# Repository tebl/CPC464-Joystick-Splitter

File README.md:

# CPC 464 Joystick splitter

Simple passive device that breaks out the joystick port on the Amstrad CPC 464 computer so that two Atari-style joysticks can be used, it is based on an article in the magazine Amstrad Action (scans available on [CPCWiki](https://www.cpcwiki.eu/index.php/Joystick_Splitter)). Note that because there are no active components, this will not work with joysticks that have any active electronics (commonly used by autofire circuits). A second fire button has also been added, this matches the pinout usually associated with Sega Master System gamepads (will not work with the controllers for Sega Genesis or Mega Drive).

There is an additional faceplate available for this project, this is mainly there to add the appearance of putting it all in a box without breaking out a hacksaw. This is completely optional and don't serve any purpose other than making it all look rather stylish (mostly according to me). I made it reversible so that two designs could be featured, graphics are not in my bag of tricks - so at the moment they should be considered placeholders.

- [1> Building the unit](#1-building-the-unit)
  - [1.1> Soldering it together](#11-soldering-it-together)
  - [1.2> Assembling the unit](#12-assembling-the-unit)
  - [1.3> Cable bits](#13-cable-bits)
  - [1.4> Testing it out](#14-testing-it-out)
- [2> Schematic](#2-schematic)
- [3> BOM](#3-bom)

# 1> Building the unit
Building the unit assumes you have at least minor experience soldering things together, recommended is at least a soldering station with adjustable temperature to get started - usually you'll want some 60/40 solder tin (if you can get that where you live). With the equipment sorted, now comes the shopping. So head on over to the [BOM](#3-bom)-section for some information on what you need, with ebay, AliExpress and similar sites you'll need to treat these as a starting search term and get what seems to match the gallery pictures.

## 1.1> Soldering it together
The construction of this unit should be straight-forward, observe the direction of the diodes and solder those in first. Next, solder in the IDC socket, the gap should point inwards and will match the illustration on the board itself. Right-angle DB9 should be straight-forward as well, just slot them in place and solder - take care when soldering the anchors on the sides, heat quickly travels to the other side so don't hold your finger on any of the metal.

## 1.2> Assembling the unit
The faceplate can be reversed to match the look you want the unit to have, at some point in the far flung future I'll hopefully have some 1bit artwork suitable to put on it. If you bought the *M3 nylon hex kit* as suggested, you can use four of the 6mm tall standoffs on each corner of the main PCB - fix them on the bottom using M3 nuts (snip off the remaining part of the nylon screw). Place the faceplate on top, screw it into place using - well - M3 nylon screws. Use wire cutters to cut off any metal parts protruding further down than the M3 nuts, this is just so that nothing messes up your desk surface.

At this point you might be wondering about the extra holes at the back. If not, then you're almost done - skip to the [cable bits](#13-cable-bits). Still here? ... The idea of the holes was that they're there in case you can find some M3 brass female to female hex spacers, screw them into place from the underside to add some more weight to the back of the unit.

## 1.3> Cable bits
I've gone into extensive detail on making up the joystick cables, so for a more detailed explanation skip on over to the [C64 JoyKEY](https://github.com/tebl/C64-JoyKEY/blob/main/documentation/building.md#building-the-cables) documentation to see how I did it there. Essentially you just take a *2x5 pin IDC JTAG AVR cable* (common ebay listing description), find the end that fits nicely into the keying on the board and cut off the other. Take a female IDC flat cable DB9 connector, match up pin 1 with the red stripe on the cable and squeeze really hard with something to lock it into place on the cable. Wrap the cable over and push the strain relief on the connector.

## 1.4> Testing it out
Given the way the Amstrad CPC was constructed, testing actually don't require any software at all - just plug it in and try messing around with the joystick. If it works you'll see characters printed on the screen, this is because the joystick is electrically linked with the keyboard so it'll register as key presses.

From a technical point of view I don't know if this was pure genius, or just a very cheap hack done in order to save money. I'm leaning toward the latter as it mostly meant that the cost-cutting measures saved them a single joystick connector as well as at most a chip or two, loosing support for common Atari-style joysticks with autofire at the same time.

As already mentioned the splitter allows the use of Atari-style joysticks with a standard pinout, but while I've tested a few - there are only a limited selection that support actually support two fire buttons. The one I've tested are as follows:
- ArcadeR (RetroRadionics)
- [C64 JoyKEY](https://github.com/tebl/C64-JoyKEY/blob/main/documentation/configuration.md#11-amstrad-cpc-464)
- Sega Master System gamepads

# 2> Schematic
The supplied KiCad files should be sufficient as both a schematic and as a  starting point for ordering PCBs (basically you could just zip the contents of the export folder and upload that on a fabrication site), the schematic is also available in [PDF-format](documentation/schematic) and this is what you'll need to print and work your way through this things don't work as expected after assembly.

# 3> BOM
Most parts should be easy to get a hold of from your favourite local electronic component shop, but given that I don't have access to such shops where I live so everything was based on whatever I could get cheapest from eBay/AliExpress (free shipping, but plan on waiting 3-4 weeks for delivery).

| Reference     | Item                                                           | Count | Order  |
| ------------- | -------------------------------------------------------------- | ----- | ------ |
| PCB           | Fabricate using Gerber files                                   |     1 | [PCBWay](https://www.pcbway.com/project/shareproject/CPC464_Joystick_Splitter.html) |
| PCB Faceplate | Fabricate using Gerber files                                   |    (1)| [PCBWay](https://www.pcbway.com/project/shareproject/CPC464_Joystick_Splitter__Faceplate_A1_.html) |
| D1-D12        | 1n4148 diode DO-35                                             |    12 |        | 
| J1,J2         | Female DB9 right-angle connector                               |     2 |        |
| J3 *          | 2x5 pin male IDC socket                                        |     1 |        |
| DB9 cable **  | Ribbon cable (9 wires), DB-9 female IDC and 2x5 pin female IDC |     1 |        |
| Mounting ***  | M3x6mm nylon HEX standoff                                      |    (4)|        |
| Mounting ***  | M3x6mm nylon hex screw                                         |    (4)|        |
| Mounting ***  | M3 nylon nut                                                   |    (4)|        |

*) Can use regular double row pin headers, but it is recommended to use IDC socket as it has keying.

**) You can buy the ribbon cable, DB9 female IDC connector and 2x5 pin female IDC. The easiest however is just buying something that already has the female DB9 connector attached to a ribbon cable, then just cut off the DB9 end - finally, add the 2x5 pin female IDC connector. Pictures on my [C64 JoyKEY](https://github.com/tebl/C64-JoyKEY/blob/main/documentation/building.md#building-the-cables)-repository as that uses the exact same cable.

***) The easiest way of ordering these is to just one of the M3 nylon standoff kits on ebay, AliExpress or any similar sites. That way you'll get more than what you need in various sizes for future projects as well.

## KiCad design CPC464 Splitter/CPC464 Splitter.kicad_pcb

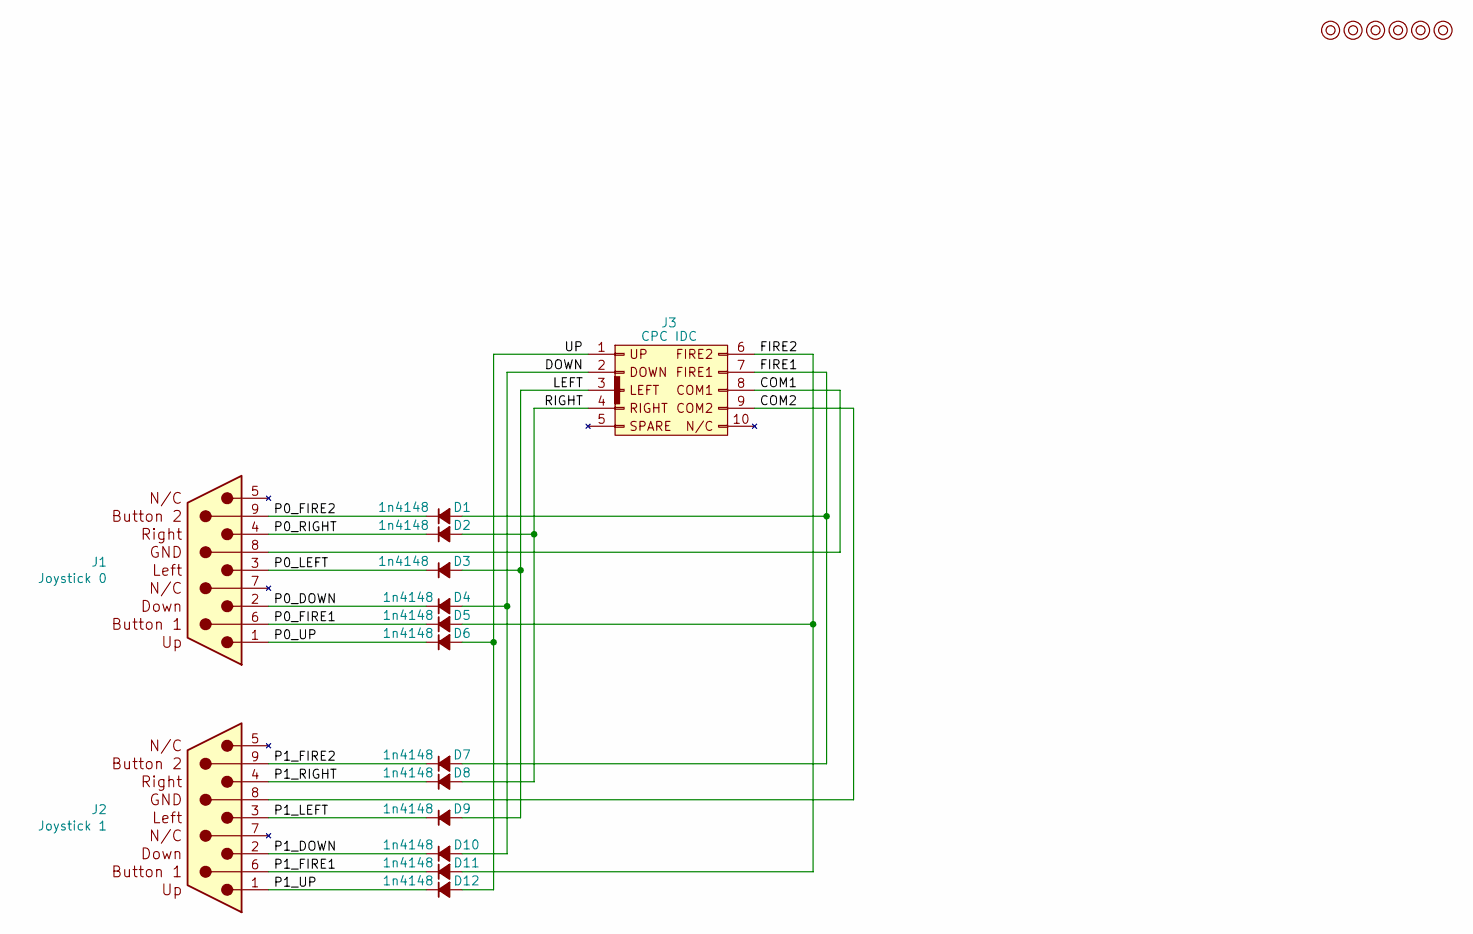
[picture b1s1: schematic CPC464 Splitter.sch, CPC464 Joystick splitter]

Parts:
D1, D2, D3, D4, D5, D6, D7, D8, D9, D10, D11, D12: 1n4148; D_DO-35_SOD27_P7.62mm_Horizontal
J1: Joystick 0; DSUB-9_Male_Horizontal_P2.77x2.84mm_EdgePinOffset7.70mm_Hou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
J2: Joystick 1; DSUB-9_Male_Horizontal_P2.77x2.84mm_EdgePinOffset7.70mm_Hou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
J3: CPC IDC; IDC_Joystick
M1, M2, M3, M4, M5, M6: Mounting; M3_pin

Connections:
/COM1: J1.8 (GND), J3.8
/COM2: J2.8 (GND), J3.9
/DOWN: D4.2 (A), D10.2 (A), J3.2
/FIRE1: D1.2 (A), D7.2 (A), J3.7
/FIRE2: D5.2 (A), D11.2 (A), J3.6
/LEFT: D3.2 (A), D9.2 (A), J3.3
/P0_DOWN: D4.1 (K), J1.2
/P0_FIRE1: D5.1 (K), J1.6
/P0_FIRE2: D1.1 (K), J1.9
/P0_LEFT: D3.1 (K), J1.3
/P0_RIGHT: D2.1 (K), J1.4
/P0_UP: D6.1 (K), J1.1
/P1_DOWN: D10.1 (K), J2.2
/P1_FIRE1: D11.1 (K), J2.6
/P1_FIRE2: D7.1 (K), J2.9
/P1_LEFT: D9.1 (K), J2.3
/P1_RIGHT: D8.1 (K), J2.4
/P1_UP: D12.1 (K), J2.1
/RIGHT: D2.2 (A), D8.2 (A), J3.4
/UP: D6.2 (A), D12.2 (A), J3.1

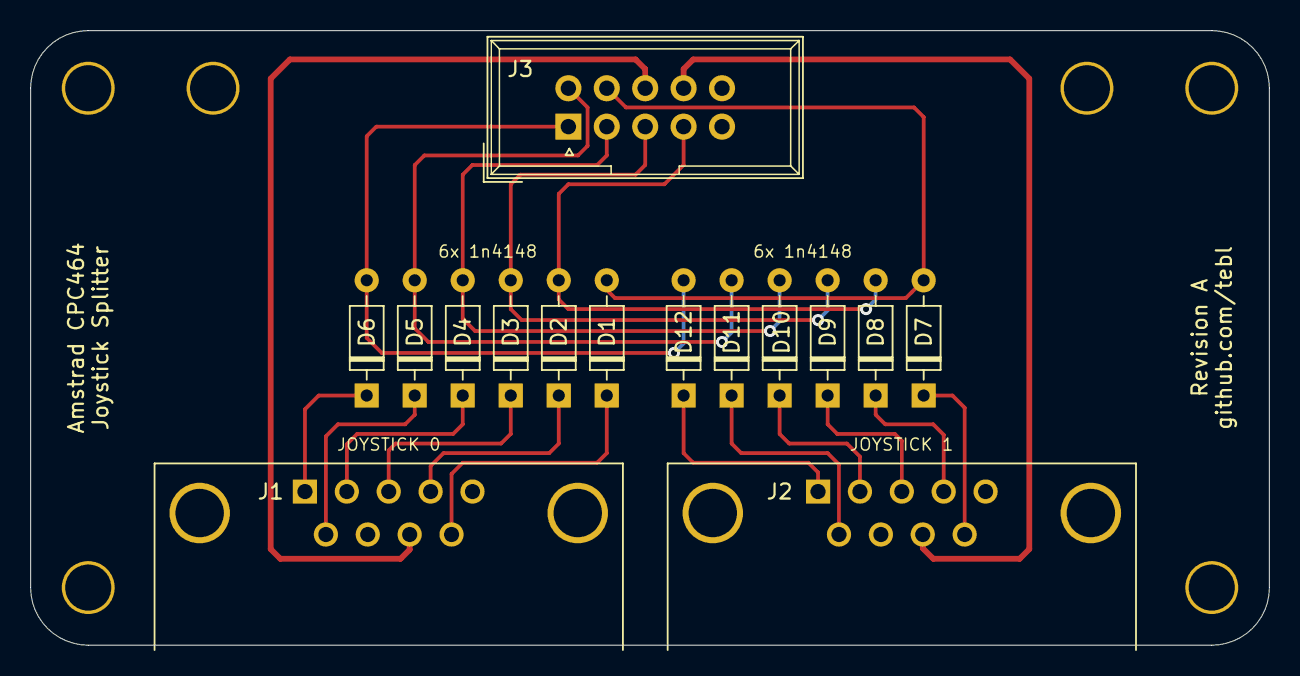
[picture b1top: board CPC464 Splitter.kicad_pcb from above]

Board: 2 copper layers, 81.9 x 40.6 mm, 21 parts (0 on the bottom side), 20 nets.

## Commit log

2021-01-10 Schematic done
2021-01-10 Layout done
2021-01-10 Added outline for faceplate
2021-01-10 Restored schematic
2021-01-10 Added reversible faceplate
2021-01-10 Add license
2021-01-10 Updated gerbers
2021-01-13 README placeholder
2021-01-13 Added README contents
2021-01-26 Adjusted cutouts
2021-02-05 Added gallery images
2021-02-05 Added README content
2021-02-05 Added README index
2021-02-05 Added controller suggestions
2021-02-05 Added PCBWay urls
